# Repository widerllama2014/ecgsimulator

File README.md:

# 3-Lead ECG Simulator (ESP32-CAM)

Low-cost, open-hardware simulator that outputs the limb leads **DI, DII and DIII** at
millivolt level, as a safe test source for ECG monitors and readers. An ESP32-CAM
generates two PWM signals; each one goes through a two-stage RC filter and a 1:1101
voltage divider to reach physiological amplitude.

> **Not a medical device. Never connect it to a person.** It is meant to feed ECG
> monitors, acquisition boards and oscilloscopes for testing and teaching.

Project 5, *Biomedical Signal Simulator*, group 13. Electrónica Biomédica
(IBB224S-1), Universidad del Desarrollo (UDD), Chile, 2026.

| Team member | E-mail | Main role |
|---|---|---|
| José Tomás Romero | jt.romeroreyes@udd.cl | Schematic, PCB, BOM, final prototype and Git repository |
| Benjamín Garrido | b.garridob@udd.cl | First prototype and first circuit design (on paper), firmware, software and measurements |

Shared by both: research and writing of the reports.

Professors: Alejandro Rebolledo and Wladimir Araya. Teaching assistant: Nicolas Walker.

---

## Status and presented version

- **Presented version:** the last commit of the `main` branch, running on the **PCB v2**
  board (milled in the lab and fixed by hand to match the v3 design).
- **Part I** (proposal and requirements) and **Part II** (electronic design and PCB):
  delivered, see `docs/informes/`.
- **Works:** tested on a breadboard with an oscilloscope: the four rhythms (40, 60, 120
  and 180 bpm), the 1 mV calibration pulse, the vector-mode scenarios and WiFi control.
  Results are in the final report.
- **PCB:** v2 milled and fixed by hand to match v3. v3 is the final design and was not
  milled again.
- **Pending:** oscilloscope test of the PCB, integration test with a real ECG reader
  (Project 4, groups 5 and 11), testing the EMG mode on hardware, a 10-measurement
  series per rhythm, and making the blue LED on IO12 work.

## Architecture

```
 POWER
   USB-C ──► TP4056 (charger) ──► SW1 ON/OFF ──► MT3608 (boost, set to 5.0 V) ──► 5 V ──► ESP32-CAM
                 ▲                                                                  └──► green LED (ON)
                 └── LiPo 1S 3.7 V, 1000 mAh (B+ / B−)

 SIGNAL (one RC filter and one 1:1101 divider per channel)
   ESP32-CAM ─┬─ IO14 (PWM) ──► RC filter ──► TP1 ──► 220 kΩ / 200 Ω ──► LA electrode
              └─ IO13 (PWM) ──► RC filter ──► TP2 ──► 220 kΩ / 200 Ω ──► LL electrode
                                     RA electrode ── 200 Ω ── GND       RL electrode ── GND

 INTERFACES
   SW2 (IO15) ──► change mode              GPIO33 ──► on-board red LED, blinks with each beat
   WiFi network "Simulador-ECG" ──► web page at 192.168.4.1 (phone or PC)
   USB serial, 115200 baud ──► Arduino Serial Monitor or software/vector_ecg.py
```

Each RC filter has two stages: 1 kΩ / 100 nF followed by 10 kΩ / 10 nF.

**The simulator works without any external application.** The whole signal is
generated on the ESP32-CAM, and the control web page is served by the board itself.
The PC tools in `software/` are optional.

**Main files:**

- **Schematic:** [KiCad](electronica/kicad/Proyecto%20de%20prueba.kicad_sch) ·
  [PDF](electronica/outputs/Esquematicopdf.pdf) · [PNG](electronica/outputs/imagenes/Esquematico.png)
- **PCB:** [KiCad](electronica/kicad/Proyecto%20de%20prueba.kicad_pcb) ·
  [PDF](electronica/outputs/PCBpdf.pdf) · [PNG](electronica/outputs/imagenes/PCB.png) ·
  [3D (STEP)](electronica/outputs/ECG.step)
- **Firmware:** [simulador_ecg_2canales.ino](firmware/simulador_ecg_2canales/simulador_ecg_2canales.ino) ·
  [simulador_ecg_wifi.ino](firmware/simulador_ecg_wifi/simulador_ecg_wifi.ino)
- **Software:** [vector_ecg.py](software/vector_ecg.py) ·
  [banco_virtual_ecg.html](software/banco_virtual_ecg.html)

### How the signal works

- Each channel turns the PWM into a smooth voltage (both filter stages cut at ≈1.6 kHz)
  and divides it by **1101**, so **1 mV at the electrode = 1.101 V at the test point**.
- An ECG monitor only measures differences between electrodes, so two channels are
  enough for the three limb leads:
  - **DI = LA − RA** (channel 1)
  - **DII = LL − RA** (channel 2)
  - **DIII = LL − LA**, computed by the monitor itself, so Einthoven's law
    (DII = DI + DIII) always holds.
- RA is the zero of the lead differences (200 Ω to GND, the same output impedance as
  LA and LL). RL is the monitor's reference and goes straight to GND.
- The heartbeat is a sum of Gaussian waves (P, Q, R, S and T) stored as a table and
  played back one sample per millisecond from a 1 ms hardware timer.

## Hardware

| Part | Function | Datasheet |
|---|---|---|
| ESP32-CAM (AI-Thinker) | Generates both PWM channels, creates its own WiFi network and serves the control web page | [esp32cam.pdf](docs/datasheets/esp32cam.pdf) |
| TP4056 module (USB-C) | Charges the battery | [TP4056.PDF](docs/datasheets/TP4056.PDF) |
| LiPo 1S, 3.7 V, 1000 mAh (LP803040) | Power supply, no mains connection | [LP803040](docs/datasheets/LP803040-1000mAh-datasheet.pdf) |
| MT3608 boost module | Raises the battery voltage to 5 V for the ESP32-CAM | [MT3608.pdf](docs/datasheets/MT3608.pdf) |
| KCD1-101F switch (SW1) | Power on/off | [KCD1-101F.pdf](docs/datasheets/KCD1-101F.pdf) |
| SW2 | Mode button (IO15) | |
| 4 × ECG snap connectors | Electrodes RA, LA, LL and RL, soldered on copper pads | |
| R 1 kΩ, 10 kΩ, 220 kΩ, 200 Ω; C 100 nF, 10 nF | RC filter and divider, one set per channel | |
| LEDs + 330 Ω | Green: power on (5 V). Blue: IO12 (not used by the current firmware) | |

The battery wires are soldered to the B+/B− pads of the TP4056 module.
**Set the MT3608 output to 5.0 V with its trimmer before plugging in the ESP32-CAM.**

### ESP32-CAM pins

| Pin | Use |
|---|---|
| IO14 | PWM, channel LA (DI) |
| IO13 | PWM, channel LL (DII) |
| IO15 | Mode button (to GND) |
| IO12 | Blue LED on the PCB. Not functional yet: the firmware reads IO12 as the start/stop button |
| GPIO33 | On-board red LED, blinks with each R wave |
| IO4 | Camera flash, kept off |

The camera and the microSD slot use most of the remaining pins: run the simulator
**without a microSD card** and do not press buttons while the board boots, because
IO2, IO12 and IO15 are strapping pins.

### Test points

| Test point | Signal |
|---|---|
| TP1 | Channel LA, in volts |
| TP2 | Channel LL, in volts |
| TP3 | GND, for the oscilloscope ground clip |

The electrodes are at millivolt level, so measure at the test points and convert:
`V_TP = baseline + 1.101 × mV`. The baseline is 0.80 V with the 2-channel firmware
and 1.55 V with the vector/WiFi firmware. For DIII, measure between TP1 and TP2 with a
battery-powered oscilloscope.

> **On the presented v2 board** the test points differ from v3. After the manual fix,
> the test point marked **TP1 carries channel LL**, and channel LA has no test point:
> measure it on the lead of **C5** that is not connected to GND. The GND test point is
> the same.

## PCB

- KiCad 10 project: `electronica/kicad/Proyecto de prueba.kicad_pro`. The design files
  are **v3**, the final version.
- 90 × 130 mm, single-sided, all tracks on **B.Cu** (no vias), designed for the lab CNC
  with 0.8 mm minimum track width and 0.8 mm clearance.
- The board milled in the lab is **v2**. It was brought up to v3 by hand: two track
  cuts to separate the channels, C7 replaced by a 200 Ω resistor (RA to GND) and a
  10 nF capacitor added to the LL channel. With this fix, v2 and v3 work the same way
  in practice; the only difference is that v2 has fewer test points.
- The electrode snaps were reused from disposable ECG electrodes, because we could not
  find them for sale. Each electrode was cut down to its snap, the top and bottom
  parts were separated, and only the top stud was mounted. Its material cannot be
  soldered, so it was fixed to the copper pad with white PVA glue (*cola fría*) on the
  edges only; the underside of the stud rests directly on the pad, and the electrical
  connection was checked.
- Four Ø3.2 mm mounting holes near the corners.
- The electrode snaps, both switches and the MT3608 module are mounted on the bottom
  side, which is the side facing the user.
- Custom symbols, footprints and 3D models are in `electronica/libraries/`
  (`proyecto_ECG.kicad_sym`, `proyecto_ECG.pretty/`, `3dmodels/`). All library and
  3D-model paths are relative to the project, so it opens on any computer.

| Fabrication file | Content |
|---|---|
| [`electronica/outputs/GERBER.zip`](electronica/outputs/GERBER.zip) | Gerbers (B.Cu, F.Cu, Edge.Cuts, F.Silkscreen) and drill files (PTH, NPTH) |
| [`electronica/outputs/MATERIALES_ECG.csv`](electronica/outputs/MATERIALES_ECG.csv) | Bill of materials (BOM) |
| [`electronica/outputs/ECG.step`](electronica/outputs/ECG.step) | 3D model of the assembled board |
| [`electronica/outputs/Esquematicopdf.pdf`](electronica/outputs/Esquematicopdf.pdf) | Schematic (PDF) |
| [`electronica/outputs/PCBpdf.pdf`](electronica/outputs/PCBpdf.pdf) | PCB views (PDF) |
| [`electronica/outputs/imagenes/`](electronica/outputs/imagenes) | Schematic and PCB (PNG), 3D renders (front and back) |

## Firmware (Arduino IDE)

- **Board:** AI Thinker ESP32-CAM, programmed through the **ESP32-CAM-MB** base.
- **Tools:** Arduino IDE 2 with the board package **esp32 by Espressif Systems**
  (tested with version 3.3.12).
- **Dependencies:** none beyond the board package. `WiFi.h` and `DNSServer.h` come
  with it.

**To compile and upload:**

1. In Arduino IDE, open *File → Preferences* and add this URL to *Additional boards
   manager URLs*: `https://espressif.github.io/arduino-esp32/package_esp32_index.json`
2. Open *Tools → Board → Boards Manager* and install **esp32 by Espressif Systems**.
3. Open the sketch, for example
   `firmware/simulador_ecg_2canales/simulador_ecg_2canales.ino`. For the WiFi version,
   `pagina.h` must stay in the same folder as `simulador_ecg_wifi.ino`.
4. Remove the microSD card, plug the ESP32-CAM into the ESP32-CAM-MB base and connect
   it to the computer by USB.
5. In *Tools → Board*, choose **AI Thinker ESP32-CAM**, and in *Tools → Port*, the COM
   port of the base.
6. Click *Upload*. The base resets the board by itself, so no buttons are needed.
7. Open the Serial Monitor at **115200 baud** and press the RST button on the board.

| Sketch | What it does |
|---|---|
| [`firmware/simulador_ecg_2canales`](firmware/simulador_ecg_2canales) | Main program: 40, 60, 120 and 180 bpm, 1 mV / 1 Hz calibration pulse, ×1/×2 amplitude, start/stop, beat LED |
| [`firmware/simulador_ecg_wifi`](firmware/simulador_ecg_wifi) | Cardiac-vector mode plus a web page served over WiFi (see its [LEEME_wifi.md](firmware/simulador_ecg_wifi/LEEME_wifi.md)) |
| [`firmware/Versiones Anteriores`](firmware/Versiones%20Anteriores) | Earlier versions, in chronological order ([LEEME_versiones.md](firmware/Versiones%20Anteriores/LEEME_versiones.md)) |

**Vector mode.** The heart is modelled as a 3D dipole; each electrode sees its
projection, so the same circuit shows six scenarios: normal axis, left axis deviation,
right axis deviation, RA–LA cables swapped, LA–LL cables swapped and dextrocardia. The
axis can be rotated freely and the electrodes can be moved.

**WiFi control.** The board creates its own network, **Simulador-ECG** (password
`ecg12345`). Open **http://192.168.4.1** on a phone or computer to see DI, DII and DIII,
drag the electrodes, change rhythm and scenario, and start or stop the output. No
internet is needed, so the simulator can run on battery, isolated from mains, while it
feeds a monitor.

**EMG mode (experimental).** A surface-EMG burst (1 s on, 1 s off, 20–450 Hz,
≈0.2 mV RMS) on channel LA. It is programmed but not yet tested on hardware.

## Software

| File | What it does |
|---|---|
| [`software/vector_ecg.py`](software/vector_ecg.py) | Desktop viewer for the vector mode: drag the electrodes on a body and see DI, DII, DIII and the heart vector in 3D |
| [`software/banco_virtual_ecg.html`](software/banco_virtual_ecg.html) | Virtual test bench: simulated board, circuit, oscilloscope and multimeter, to practice measurements before the lab |

**vector_ecg.py**

- **Dependencies:** Python 3 and `pip install pyserial matplotlib numpy`.
- **Without the board:** `python vector_ecg.py --demo`
- **With the board:** load `simulador_ecg_wifi` (it accepts the same serial commands as
  the earlier vector-mode sketch), connect the board by USB, **close the Arduino Serial
  Monitor**, and run `python vector_ecg.py --puerto COM5`. Use the board's port (on
  Mac/Linux, something like `/dev/ttyUSB0`). The program talks to the board over USB
  serial at 115200 baud.

**banco_virtual_ecg.html** opens in any web browser and does not connect to the board.

## Initial check

After uploading the firmware and turning the simulator on, you should see:

1. **Power:** with SW1 on, the green LED lights up.
2. **Serial Monitor (115200 baud):** with the 2-channel firmware, it prints
   `PWM OK: 62500 Hz, 10 bits, 2 canales (IO14 = LA, IO13 = LL)` and then
   `Modo: 60 lpm | R: DI 0.80, DII 1.00, DIII 0.20 mV`. The simulator starts at 60 bpm
   and the red LED on the ESP32-CAM blinks with each beat.
3. **Multimeter (DC):** about **0.80 V** at each channel's test point (1.55 V with the
   WiFi firmware). On the v2 board, see the note under *Test points*.
4. **Oscilloscope:** DC coupling, ×1 probe, 500 mV/div and 200 ms/div, with the ground
   clip on the GND test point. Channel LA swings between about 0.76 and 1.68 V and
   channel LL between about 0.50 and 1.90 V, one beat per second.
5. **Mode button:** each press of SW2 moves to the next mode (40, 60, 120, 180 bpm and
   calibration), and the Serial Monitor confirms the change.
6. **WiFi firmware:** the network **Simulador-ECG** (password `ecg12345`) appears.
   Open **http://192.168.4.1**: the page shows DI, DII and DIII and says
   **PLACA CONECTADA**.

To feed an ECG monitor, connect each monitor cable to the snap with the same name (RA,
LA, LL and RL) and run the simulator from its battery.

## Repository structure

```
.
├── README.md
├── LICENSE                     CERN-OHL-S v2
├── docs/
│   ├── bitacora.md             Development log
│   ├── datasheets/             Component datasheets
│   └── informes/               Reports: Part I, Part II and final report (PDF)
├── electronica/
│   ├── kicad/                  KiCad project (.kicad_pro, .kicad_sch, .kicad_pcb)
│   ├── libraries/              Custom symbols, footprints and 3D models
│   └── outputs/                BOM (CSV), STEP, Gerber + drill (.zip), schematic and PCB (PDF)
│       └── imagenes/           Schematic and PCB (PNG), 3D renders
├── firmware/                   ESP32-CAM sketches (current and previous versions)
└── software/                   PC tools: vector viewer and virtual bench
```

## References

- Riyanto, I. et al. (2025). Design and construction of an ECG simulator with bipolar
  leads based on the Arduino Nano microcontroller. https://doi.org/10.51747/energy.v15i2.15214
- Lynch, J. P. (2013). ECG simulator. https://www.instructables.com/ECG-Simulator/
- Microchip Technology (2020). Using PWM to generate an analog output (TB3250).
- Malmivuo, J. & Plonsey, R. (1995). *Bioelectromagnetism*. https://www.bem.fi/book/

### Sources of symbols, footprints and 3D models

| Part | Symbol and footprint | 3D model |
|---|---|---|
| ESP32-CAM | SnapMagic Search (SnapEDA): [ESP32-CAM by AI-Thinker](https://www.snapeda.com/parts/ESP32-CAM/AI-Thinker/view-part/) | Jan Ježek, GrabCAD: [ESP32-CAM](https://grabcad.com/library/esp32-cam-1) |
| MT3608 boost module | SnapMagic Search (SnapEDA): [MT3608 DC-DC Step Up Converter 2A Booster Module](https://www.snapeda.com/parts/MT3608%20DC-DC%20Step%20Up%20Converter%202A%20Booster%20Module/Generic/view-part/) | MRMS - WORKSHOP, GrabCAD: [MT3608 DC to DC Boost Converter 2 A](https://grabcad.com/library/mt3608-dc-to-dc-boost-converter-2-a-1) |
| TP4056 module (USB-C) | Made by the team (`TP4056_modulo`) | GrabCAD: *TP4056 Charging Module Type C* (STEP and Fusion 360) |
| KCD1 switch (SW1, SW2) | Made by the team (`SW_Push_2P_ECG`), measured from the physical part | Source unknown: the download record was lost |
| Electrode snap (J1–J4) | Made by the team (`conectorelectrodo`), based on KiCad's `TestPoint_Pad_D4.0mm` with the pad enlarged to 9 mm | 3D ContentCentral: [ECG Snap Button 4mm](https://www.3dcontentcentral.com/Download-Model.aspx?catalogid=171&id=1354647) |
| Resistors, capacitors, LEDs and test points | [KiCad official libraries](https://gitlab.com/kicad/libraries/kicad-footprints) | KiCad official 3D models |

## Acknowledgements

We thank:

- The **Engineering Materials Laboratory** (Laboratorio de Materiales de Ingeniería),
  for lending us instruments and a place to work.
- **Pablo Reyes**, for the ECG electrodes and for lending us an oscilloscope.
- The **Centro de Investigación en Tecnologías para la Sociedad (C+)**, for lending us
  materials and supplies, and for helping us with our questions.
- The **UDD Science Laboratory** (Laboratorio de Ciencias), for lending us the laboratory
  to work in and for providing supplies when we needed them.

## License

This project is open hardware under the **CERN Open Hardware Licence Version 2 –
Strongly Reciprocal (CERN-OHL-S v2)**. See [LICENSE](LICENSE).

You may use, study, modify, manufacture, distribute and sell the design and products
based on it, as long as every derivative is released under the same licence, the
copyright notices are kept, modifications are stated, and the design source is made
available.

```
Copyright 2026 Benjamín Garrido, José Tomás Romero

This source describes Open Hardware and is licensed under the CERN-OHL-S v2.
You may redistribute and modify this source and make products using it under
the terms of the CERN-OHL-S v2 (https://ohwr.org/cern_ohl_s_v2.txt).
This source is distributed WITHOUT ANY EXPRESS OR IMPLIED WARRANTY, INCLUDING OF
MERCHANTABILITY, SATISFACTORY QUALITY AND FITNESS FOR A PARTICULAR PURPOSE.
Please see the CERN-OHL-S v2 for applicable conditions.
Source Location: https://github.com/widerllama2014/ecgsimulator
```

## AI use statement

We used **Claude** (Anthropic) for code and research, and **Gemini** (Google) for
research as well. Claude also made the first versions of the schematic and the PCB,
which saved us a lot of time, and generated some of the symbols. In the end, all of
this was modified by us to fit what the project needed.

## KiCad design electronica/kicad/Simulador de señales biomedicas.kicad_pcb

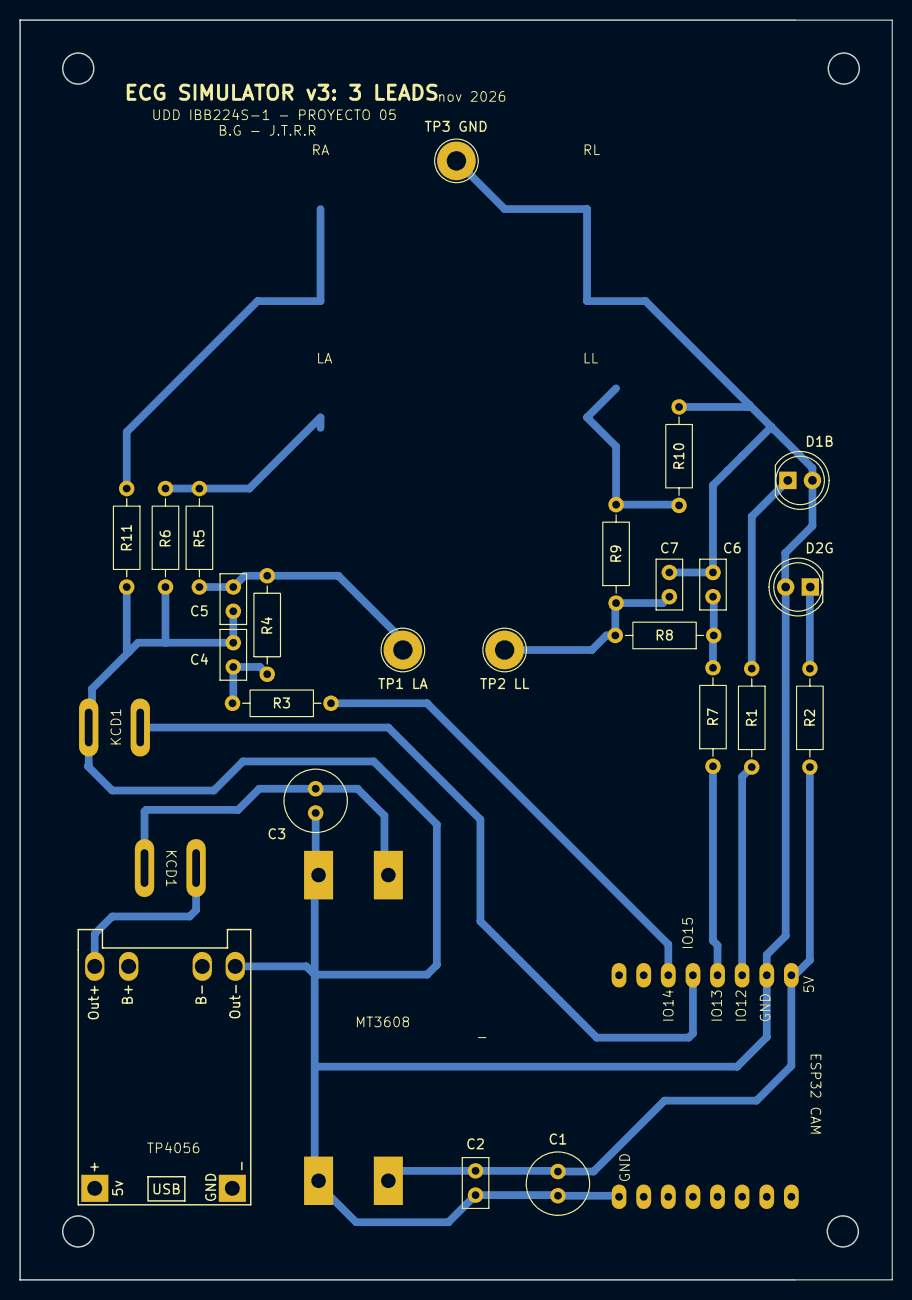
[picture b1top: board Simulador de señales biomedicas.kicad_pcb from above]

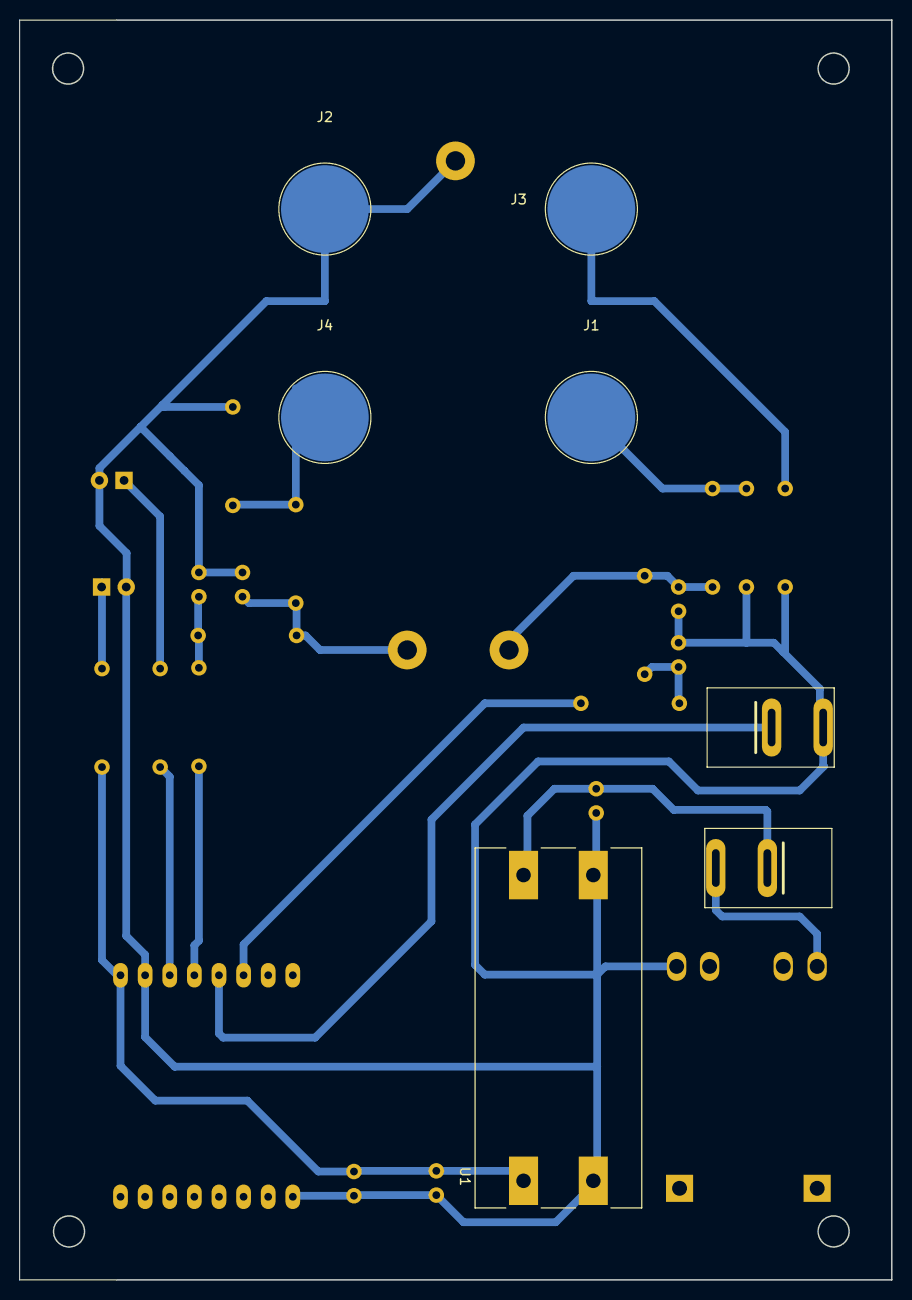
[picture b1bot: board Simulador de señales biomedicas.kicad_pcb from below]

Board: 2 copper layers, 90.0 x 130.0 mm, 32 parts (7 on the bottom side), 17 nets.

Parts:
C1, C3: 100u; C_Radial_D6.3mm_H5.0mm_P2.50mm
C2, C4, C6: 100n; C_Disc_D5.0mm_W2.5mm_P2.50mm
C5, C7: 10n; C_Disc_D5.0mm_W2.5mm_P2.50mm
D1B: AZUL_BT; LED_D5.0mm
D2G: VERDE_ON; LED_D5.0mm
J1: LA; conectorelectrodo
J2: RL; conectorelectrodo
J3: RA; conectorelectrodo
J4: LL; conectorelectrodo
R1, R2: 330; R_Axial_DIN0207_L6.3mm_D2.5mm_P10.16mm_Horizontal
R3, R7: 1k; R_Axial_DIN0207_L6.3mm_D2.5mm_P10.16mm_Horizontal
R4, R8: 10k; R_Axial_DIN0207_L6.3mm_D2.5mm_P10.16mm_Horizontal
R5, R9: 220K; R_Axial_DIN0207_L6.3mm_D2.5mm_P10.16mm_Horizontal
R6, R10, R11: 200; R_Axial_DIN0207_L6.3mm_D2.5mm_P10.16mm_Horizontal
SW1, SW2: SPST; SW_Push_2P_ECG
TP1 LA: LA; TestPoint_THTPad_D4.0mm_Drill2.0mm
TP2 LL: LL; TestPoint_THTPad_D4.0mm_Drill2.0mm
TP3 GND: GND_OSCILATOR; TestPoint_THTPad_D4.0mm_Drill2.0mm
U1: MT3608; MT3608_DC
U2: TP4056_modulo
U3: ESP32-CAM; ESP32_CAM

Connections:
/5V0: C1.1, C2.2, R2.1, U1.1 (VOUT+), U3.1 (5V)
/PWM1: R3.1, U3.6 (IO14)
/PWM3: R7.1, U3.4 (IO13)
/SW: SW2.1 (A), U3.5 (IO15)
GND: C1.2, C2.1, C3.2, C4.2, C5.2, C6.2, C7.2, D1B.2 (A), D2G.2 (A), J2.1 (~_1), R6.1, R10.1, R11.2, SW2.2 (B), TP3 GND.1 (1_1), U1.2 (VOUT-), U1.3 (VIN-), U2.3 (OUT-), U3.2 (GND), U3.9 (GND)
unnamed: C4.1, R3.2, R4.1
unnamed: C5.1, R4.2, R5.1, TP1 LA.1 (1_1)
unnamed: C6.1, R7.2, R8.1
unnamed: C7.1, R8.2, R9.1, TP2 LL.1 (1_1)
unnamed: D1B.1 (K), R1.1
unnamed: D2G.1 (K), R2.2
unnamed: J1.1 (~_1), R5.2, R6.2
unnamed: J3.1 (~_1), R11.1
unnamed: J4.1 (~_1), R9.2, R10.2
unnamed: C3.1, SW1.1 (A), U1.4 (VIN+)
unnamed: SW1.2 (B), U2.6 (OUT+)
unnamed: R1.2, U3.3 (IO12)
